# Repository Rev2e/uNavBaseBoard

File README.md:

# uNavBaseBoard
Shield for 3 uNav board

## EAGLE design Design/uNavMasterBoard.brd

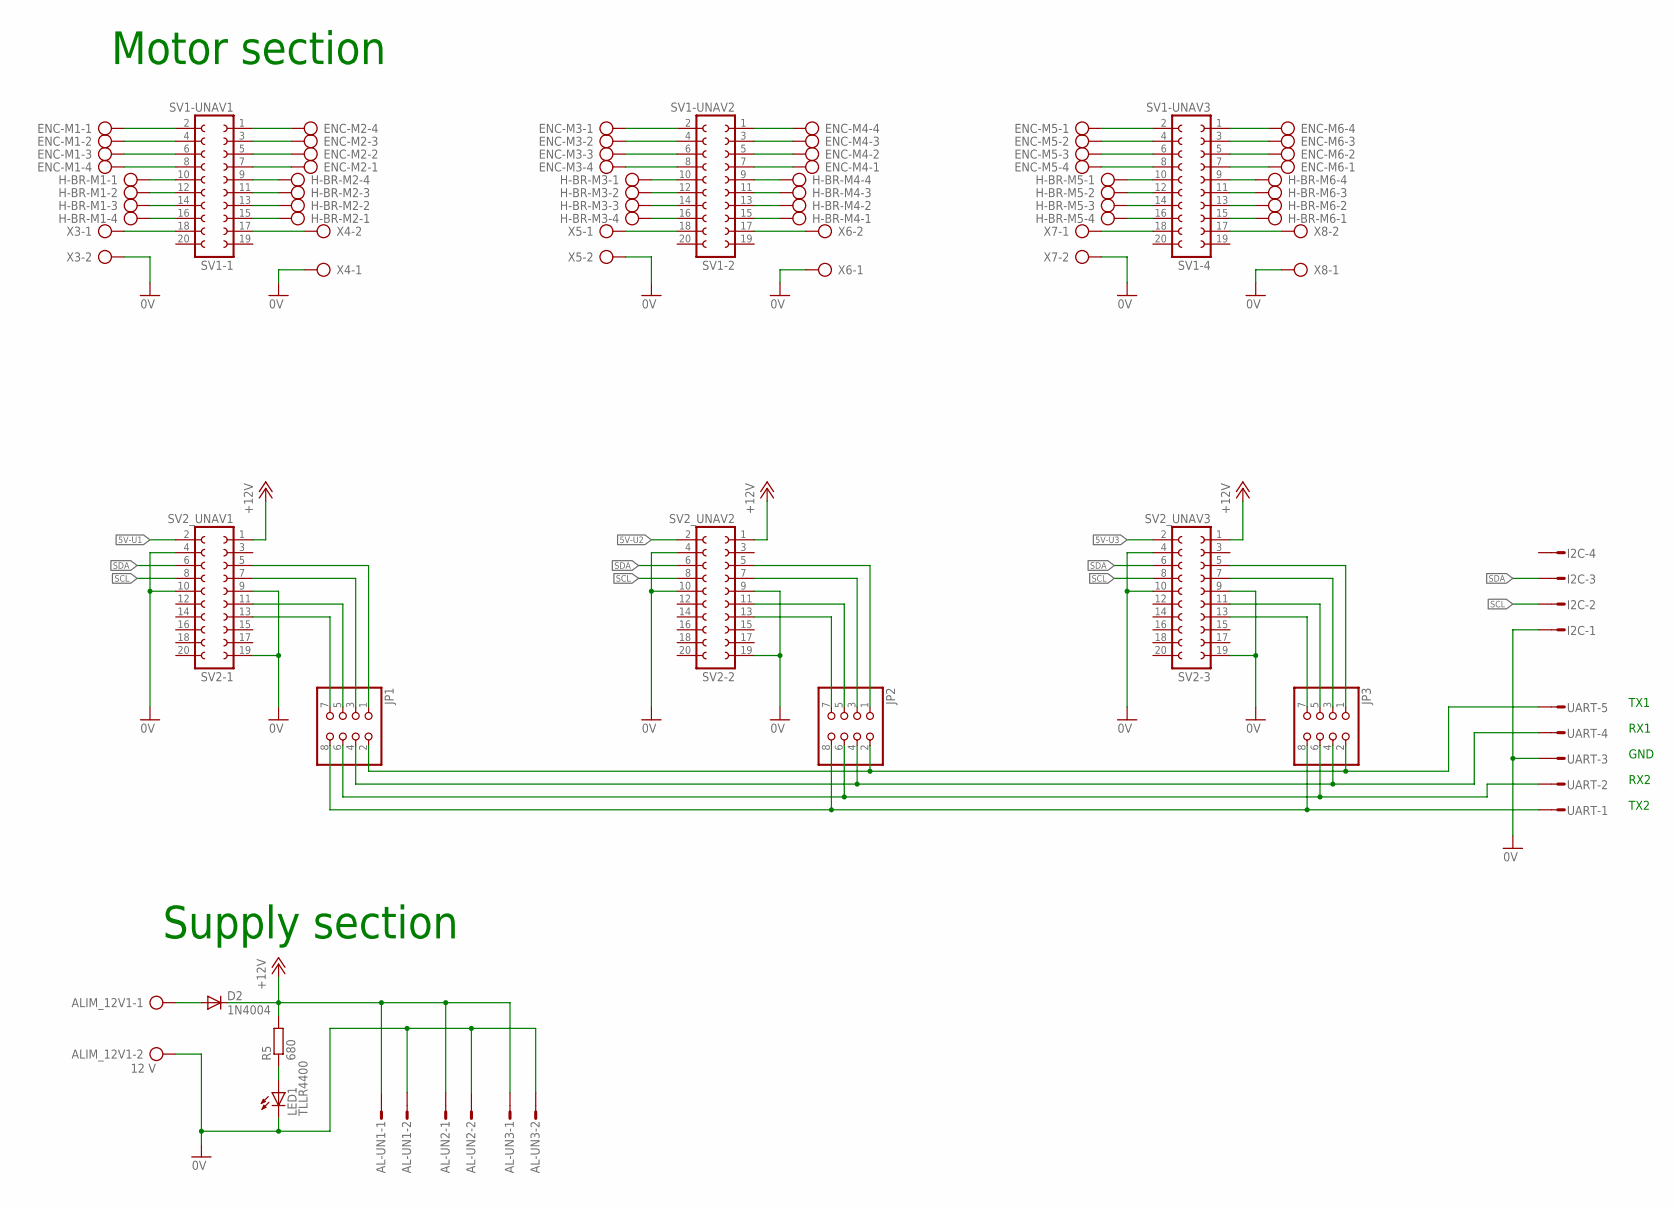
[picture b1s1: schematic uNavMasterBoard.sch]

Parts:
AL-UN1, AL-UN2, AL-UN3: S02P
ALIM_12V1: 12 V; AK500/2
D2: 1N4004; DO41-10
ENC-M1, ENC-M2, ENC-M3, ENC-M4, ENC-M5, ENC-M6: AK500/4
H-BR-M1, H-BR-M2, H-BR-M3, H-BR-M4, H-BR-M5, H-BR-M6: AK500/4
I2C: S04P
JP1, JP2, JP3: PINHD-2X4; 2X04
LED1: TLLR4400; LED3MM
R5: 680; 0207/10
SV1-1: SV1-UNAV1; FE10-2
SV1-2: SV1-UNAV2; FE10-2
SV1-4: SV1-UNAV3; FE10-2
SV2-1: SV2_UNAV1; FE10-2
SV2-2: SV2_UNAV2; FE10-2
SV2-3: SV2_UNAV3; FE10-2
UART: S05P
X3, X4, X5, X6, X7, X8: AK500/2

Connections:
0V: AL-UN1.2, AL-UN2.2, AL-UN3.2, ALIM_12V1.2, I2C.1, LED1.K (C), SV2-1.4, SV2-1.9, SV2-1.10, SV2-1.19, SV2-2.4, SV2-2.9, SV2-2.10, SV2-2.19, SV2-3.4, SV2-3.9, SV2-3.10, SV2-3.19, UART.3, X3.2, X4.1, X5.2, X6.1, X7.2, X8.1
5V-U1: SV2-1.2
5V-U2: SV2-2.2
5V-U3: SV2-3.2
+12V: AL-UN1.1, AL-UN2.1, AL-UN3.1, D2.C, R5.2, SV2-1.1, SV2-2.1, SV2-3.1
unnamed: ENC-M1.1, SV1-1.2
unnamed: ENC-M1.2, SV1-1.4
unnamed: ENC-M1.3, SV1-1.6
unnamed: ENC-M1.4, SV1-1.8
unnamed: H-BR-M1.1, SV1-1.10
unnamed: H-BR-M1.2, SV1-1.12
unnamed: H-BR-M1.3, SV1-1.14
unnamed: H-BR-M1.4, SV1-1.16
unnamed: SV1-1.18, X3.1
unnamed: ENC-M2.1, SV1-1.7
unnamed: ENC-M2.2, SV1-1.5
unnamed: ENC-M2.3, SV1-1.3
unnamed: ENC-M2.4, SV1-1.1
unnamed: H-BR-M2.4, SV1-1.9
unnamed: H-BR-M2.3, SV1-1.11
unnamed: H-BR-M2.2, SV1-1.13
unnamed: H-BR-M2.1, SV1-1.15
unnamed: SV1-1.17, X4.2
unnamed: ENC-M3.1, SV1-2.2
unnamed: ENC-M3.2, SV1-2.4
unnamed: ENC-M4.4, SV1-2.1
unnamed: ENC-M4.3, SV1-2.3
unnamed: ENC-M4.2, SV1-2.5
unnamed: ENC-M4.1, SV1-2.7
unnamed: JP1.1, SV2-1.5
unnamed: JP1.3, SV2-1.7
unnamed: JP1.5, SV2-1.11
unnamed: H-BR-M4.4, SV1-2.9
unnamed: JP1.7, SV2-1.13
unnamed: JP2.1, SV2-2.5
unnamed: H-BR-M4.3, SV1-2.11
unnamed: H-BR-M4.2, SV1-2.13
unnamed: H-BR-M4.1, SV1-2.15
unnamed: SV1-2.17, X6.2
unnamed: SV1-2.18, X5.1
unnamed: H-BR-M3.4, SV1-2.16
unnamed: H-BR-M3.3, SV1-2.14
unnamed: H-BR-M3.2, SV1-2.12
unnamed: H-BR-M3.1, SV1-2.10
unnamed: ENC-M3.4, SV1-2.8
unnamed: ENC-M3.3, SV1-2.6
unnamed: ENC-M5.1, SV1-4.2
unnamed: ENC-M5.2, SV1-4.4
unnamed: ENC-M5.3, SV1-4.6
unnamed: ENC-M5.4, SV1-4.8
unnamed: H-BR-M5.1, SV1-4.10
unnamed: H-BR-M5.2, SV1-4.12
unnamed: H-BR-M5.3, SV1-4.14
unnamed: H-BR-M5.4, SV1-4.16
unnamed: SV1-4.18, X7.1
unnamed: SV1-4.17, X8.2
unnamed: H-BR-M6.4, SV1-4.9
unnamed: H-BR-M6.3, SV1-4.11
unnamed: H-BR-M6.2, SV1-4.13
unnamed: H-BR-M6.1, SV1-4.15
unnamed: ENC-M6.4, SV1-4.1
unnamed: ENC-M6.3, SV1-4.3
unnamed: ENC-M6.2, SV1-4.5
unnamed: ENC-M6.1, SV1-4.7
unnamed: JP2.3, SV2-2.7
unnamed: ALIM_12V1.1, D2.A
unnamed: JP2.5, SV2-2.11
unnamed: LED1.A, R5.1
unnamed: JP2.7, SV2-2.13
unnamed: JP3.1, SV2-3.5
unnamed: JP3.3, SV2-3.7
unnamed: JP3.5, SV2-3.11
unnamed: JP3.7, SV2-3.13
unnamed: JP1.2, JP2.2, JP3.2, UART.5
unnamed: JP1.4, JP2.4, JP3.4, UART.4
unnamed: JP1.6, JP2.6, JP3.6, UART.2
unnamed: JP1.8, JP2.8, JP3.8, UART.1
SCL: I2C.2, SV2-1.8, SV2-2.8, SV2-3.8
SDA: I2C.3, SV2-1.6, SV2-2.6, SV2-3.6

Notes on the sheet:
TX1
TX2
RX1
RX2
Supply section
Motor section
GND

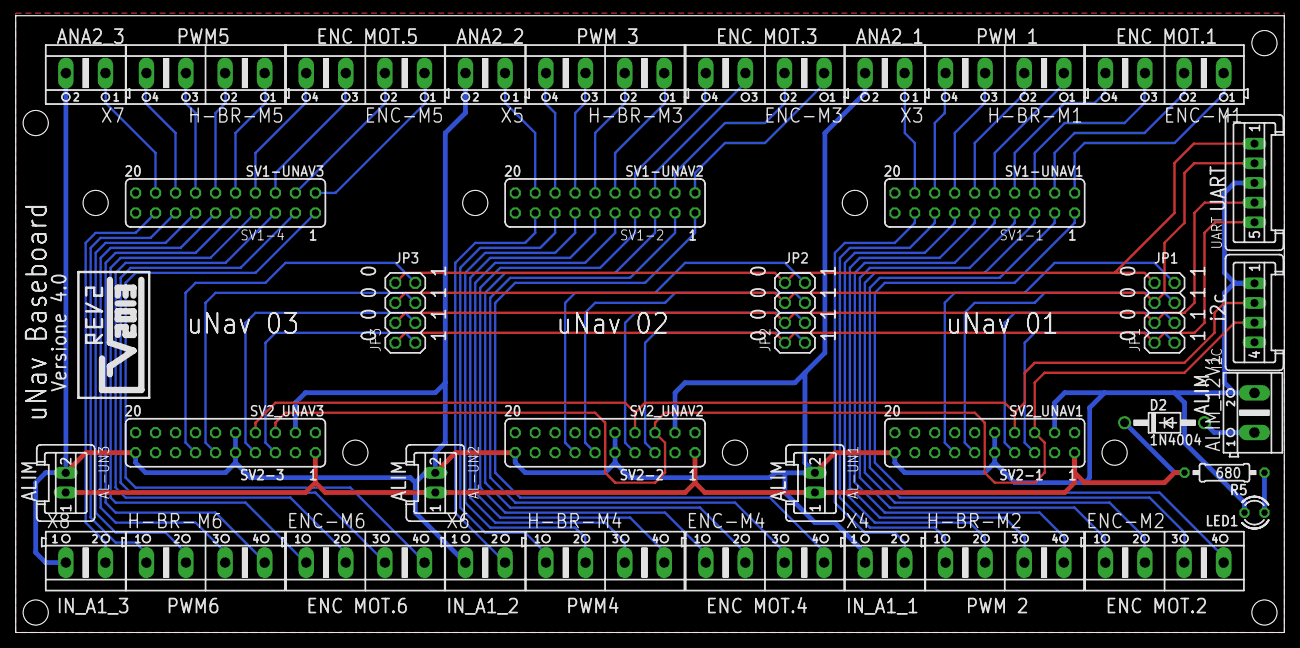
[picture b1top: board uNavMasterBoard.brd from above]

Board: 2 copper layers, 161.3 x 78.4 mm, 37 parts (0 on the bottom side), 76 nets.

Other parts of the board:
U$1: LOGO_TOP

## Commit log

2015-05-03 Project BaseBoard
2015-05-04 Fasi di lavorazione Scheda
    Fasi da inviare al Service per la creazione della Board
2015-05-05 Gerbers File
    Gerber files for the PCB Service, for the realization of the Board.
2015-05-06 Gerbers File
